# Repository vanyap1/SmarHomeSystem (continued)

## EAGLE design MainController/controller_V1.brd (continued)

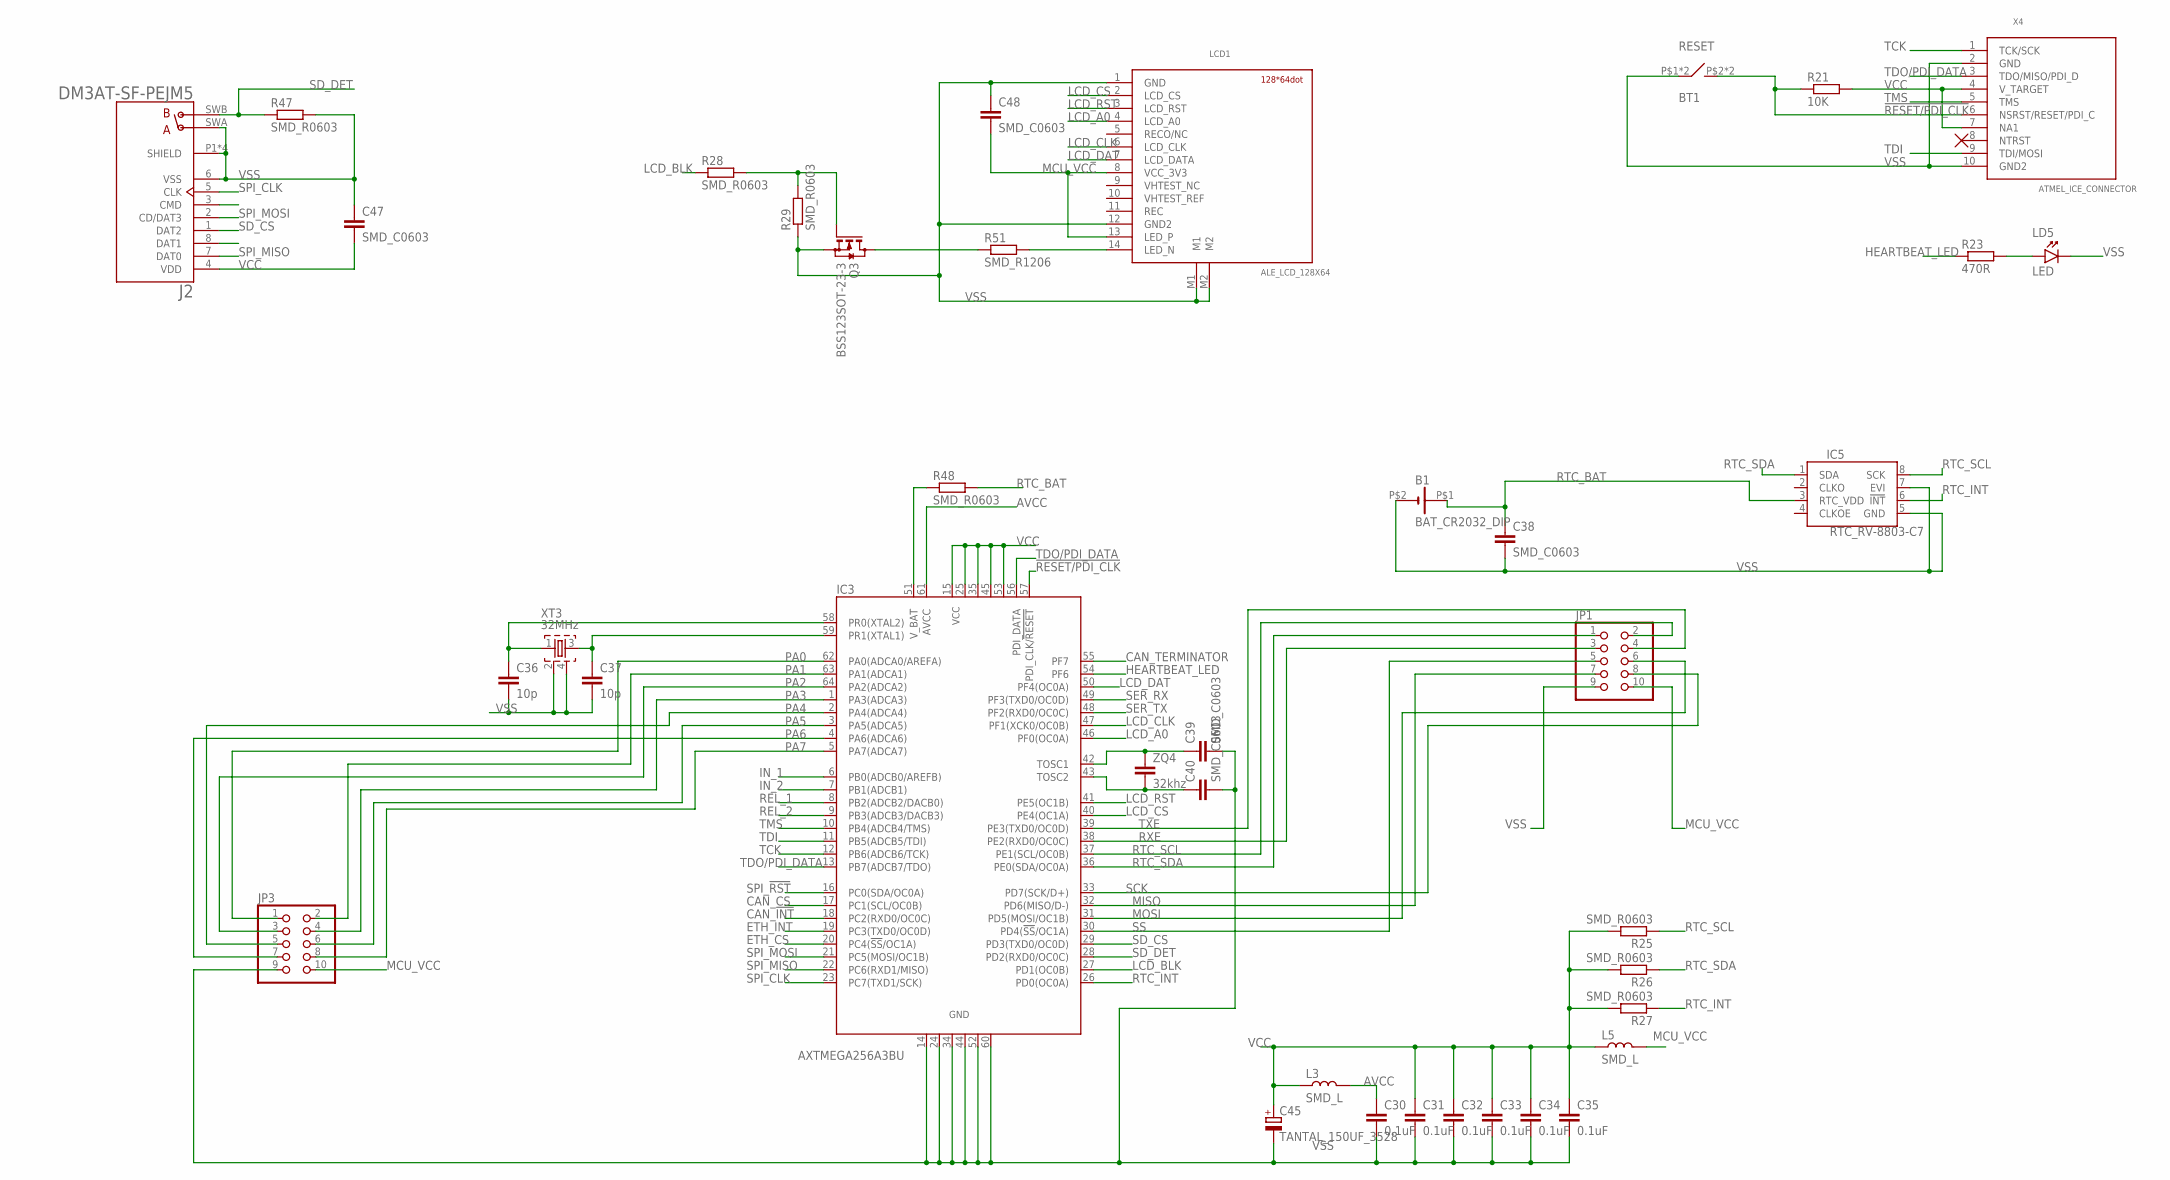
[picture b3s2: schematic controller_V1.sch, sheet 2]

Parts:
B1: BAT_CR2032_DIP; CR2032_DIP
BT1: RESET; 5X5MM_SMD_CY
C30, C31, C32, C33, C34, C35: 0.1uF; 0603
C36, C37: 10p; 0603
C38, C39, C40, C47, C48: SMD_C0603; 0603
C45: TANTAL_150UF_3528; KA-3528ASYC
IC3: AXTMEGA256A3BU; TQFP64
IC5: RTC_RV-8803-C7; C7_RTC
J2: DM3AT-SF-PEJM5; HRS_DM3AT-SF-PEJM5
JP1, JP3: PINHD-2X5; 2X05
L3, L5: SMD_L; 0805
LCD1: ALE_LCD_128X64; ALE_LCD_14PIN_CONNECTOR
LD5: LED; 3MM_DIP_LED
Q3: BSS123SOT-23-3; SOT-23(3)
R21: 10K; 0603
R23: 470R; 0603
R25, R26, R27, R28, R29, R47, R48: SMD_R0603; 0603
R51: SMD_R1206; 1206
X4: ATMEL_ICE_CONNECTOR; MINI10P_SPI/JTAG/PDI
XT3: 32MHz; QUARTZ_3X3MM
ZQ4: 32khz; 1206

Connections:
!RESET/PDI_CLK: BT1.P$2 (4), BT1.P$3 (4), IC3.57 (PDI_CLK/!RESET!), R21.1, X4.6 (NSRST/RESET/PDI_C)
AVCC: C30.1, IC3.61 (AVCC), L3.2
CAN_!INT: IC3.18 (PC2(RXD0/OC0C)); also elsewhere on the board
CAN_CS: IC3.17 (PC1(SCL/OC0B)); also elsewhere on the board
CAN_TERMINATOR: IC3.55 (PF7); also elsewhere on the board
ETH_CS: IC3.20 (PC4(!SS!/OC1A)); also elsewhere on the board
ETH_INT: IC3.19 (PC3(TXD0/OC0D)); also elsewhere on the board
HEARTBEAT_LED: IC3.54 (PF6), R23.1
IN_1: IC3.6 (PB0(ADCB0/AREFB)); also elsewhere on the board
IN_2: IC3.7 (PB1(ADCB1)); also elsewhere on the board
LCD_A0: IC3.46 (PF0(OC0A)), LCD1.4 (LCD_A0)
LCD_BLK: IC3.27 (PD1(OC0B)), R28.1
LCD_CLK: IC3.47 (PF1(XCK0/OC0B)), LCD1.6 (LCD_CLK)
LCD_CS: IC3.40 (PE4(OC1A)), LCD1.2 (LCD_CS)
LCD_DAT: IC3.50 (PF4(OC0A)), LCD1.7 (LCD_DATA)
LCD_RST: IC3.41 (PE5(OC1B)), LCD1.3 (LCD_RST)
MCU_VCC: C48.2, JP1.10, JP3.10, L5.2, LCD1.8 (VCC_3V3), LCD1.13 (LED_P); also elsewhere on the board
MISO: IC3.32 (PD6(MISO/D-)), JP1.7
MOSI: IC3.31 (PD5(MOSI/OC1B)), JP1.6
unnamed: C36.1, IC3.58 (PR0(XTAL2)), XT3.1
unnamed: C37.1, IC3.59 (PR1(XTAL1)), XT3.3
unnamed: LD5.A, R23.2
unnamed: IC3.51 (V_BAT), R48.1
unnamed: Q3.3 (D), R51.1
unnamed: LCD1.14 (LED_N), R51.2
unnamed: C40.1, IC3.43 (TOSC2), ZQ4.2
unnamed: C39.1, IC3.42 (TOSC1), ZQ4.1
unnamed: Q3.1 (G), R28.2, R29.2
PA0: IC3.62 (PA0(ADCA0/AREFA)), JP3.1
PA1: IC3.63 (PA1(ADCA1)), JP3.2
PA2: IC3.64 (PA2(ADCA2)), JP3.3
PA3: IC3.1 (PA3(ADCA3)), JP3.4
PA4: IC3.2 (PA4(ADCA4)), JP3.5
PA5: IC3.3 (PA5(ADCA5)), JP3.6
PA6: IC3.4 (PA6(ADCA6)), JP3.7
PA7: IC3.5 (PA7(ADCA7)), JP3.8
REL_1: IC3.8 (PB2(ADCB2/DACB0)); also elsewhere on the board
REL_2: IC3.9 (PB3(ADCB3/DACB3)); also elsewhere on the board
RTC_BAT: B1.P$1 (+), C38.1, IC5.3 (RTC_VDD), R48.2
RTC_INT: IC3.26 (PD0(OC0A)), IC5.6 (!INT), R27.1
RTC_SCL: IC3.37 (PE1(SCL/OC0B)), IC5.8 (SCK), JP1.2, R25.1; also elsewhere on the board
RTC_SDA: IC3.36 (PE0(SDA/OC0A)), IC5.1 (SDA), JP1.1, R26.1; also elsewhere on the board
RXE: IC3.38 (PE2(RXD0/OC0C)), JP1.3
SCK: IC3.33 (PD7(SCK/D+)), JP1.8
SD_CS: IC3.29 (PD3(TXD0/OC0D)), J2.1 (DAT2)
SD_DET: IC3.28 (PD2(RXD0/OC0C)), J2.SWB (B), R47.1
SER_RX: IC3.49 (PF3(TXD0/OC0D)); also elsewhere on the board
SER_TX: IC3.48 (PF2(RXD0/OC0C)); also elsewhere on the board
SPI_!RST: IC3.16 (PC0(SDA/OC0A)); also elsewhere on the board
SPI_CLK: IC3.23 (PC7(TXD1/SCK)), J2.5 (CLK); also elsewhere on the board
SPI_MISO: IC3.22 (PC6(RXD1/MISO)), J2.7 (DAT0); also elsewhere on the board
SPI_MOSI: IC3.21 (PC5(MOSI/OC1B)), J2.2 (CD/DAT3); also elsewhere on the board
SS: IC3.30 (PD4(!SS!/OC1A)), JP1.5
TCK: IC3.12 (PB6(ADCB6/TCK)), X4.1 (TCK/SCK)
TDI: IC3.11 (PB5(ADCB5/TDI)), X4.9 (TDI/MOSI)
TDO/PDI_DATA: IC3.13 (PB7(ADCB7/TDO)), IC3.56 (PDI_DATA), X4.3 (TDO/MISO/PDI_D)
TMS: IC3.10 (PB4(ADCB4/TMS)), X4.5 (TMS)
TXE: IC3.39 (PE3(TXD0/OC0D)), JP1.4
VCC: C31.1, C32.1, C33.1, C34.1, C35.1, C45.P (+), C47.2, IC3.15 (VCC1), IC3.25 (VCC2), IC3.35 (VCC3), IC3.45 (VCC4), IC3.53 (VCC5), J2.4 (VDD), L3.1, L5.1, R21.2, R25.2, R26.2, R27.2, X4.4 (V_TARGET), X4.7 (NA1); also elsewhere on the board
VSS: B1.P$2 (-), BT1.P$1 (1), BT1.P$4 (1), C30.2, C31.2, C32.2, C33.2, C34.2, C35.2, C36.2, C37.2, C38.2, C39.2, C40.2, C45.M (-), C47.1, C48.1, IC3.14 (GND1), IC3.24 (GND2), IC3.34 (GND3), IC3.44 (GND4), IC3.52 (GND5), IC3.60 (GND6), IC5.5 (GND), IC5.7 (EVI), J2.6 (VSS), J2.P1 (SHIELD), J2.P2 (SHIELD), J2.P3 (SHIELD), J2.P4 (SHIELD), J2.SWA (A), JP1.9, JP3.9, LCD1.1 (GND), LCD1.12 (GND2), LCD1.M1, LCD1.M2, LD5.K, Q3.2 (S), R29.1, R47.2, X4.2 (GND), X4.10 (GND2), XT3.2, XT3.4; also elsewhere on the board

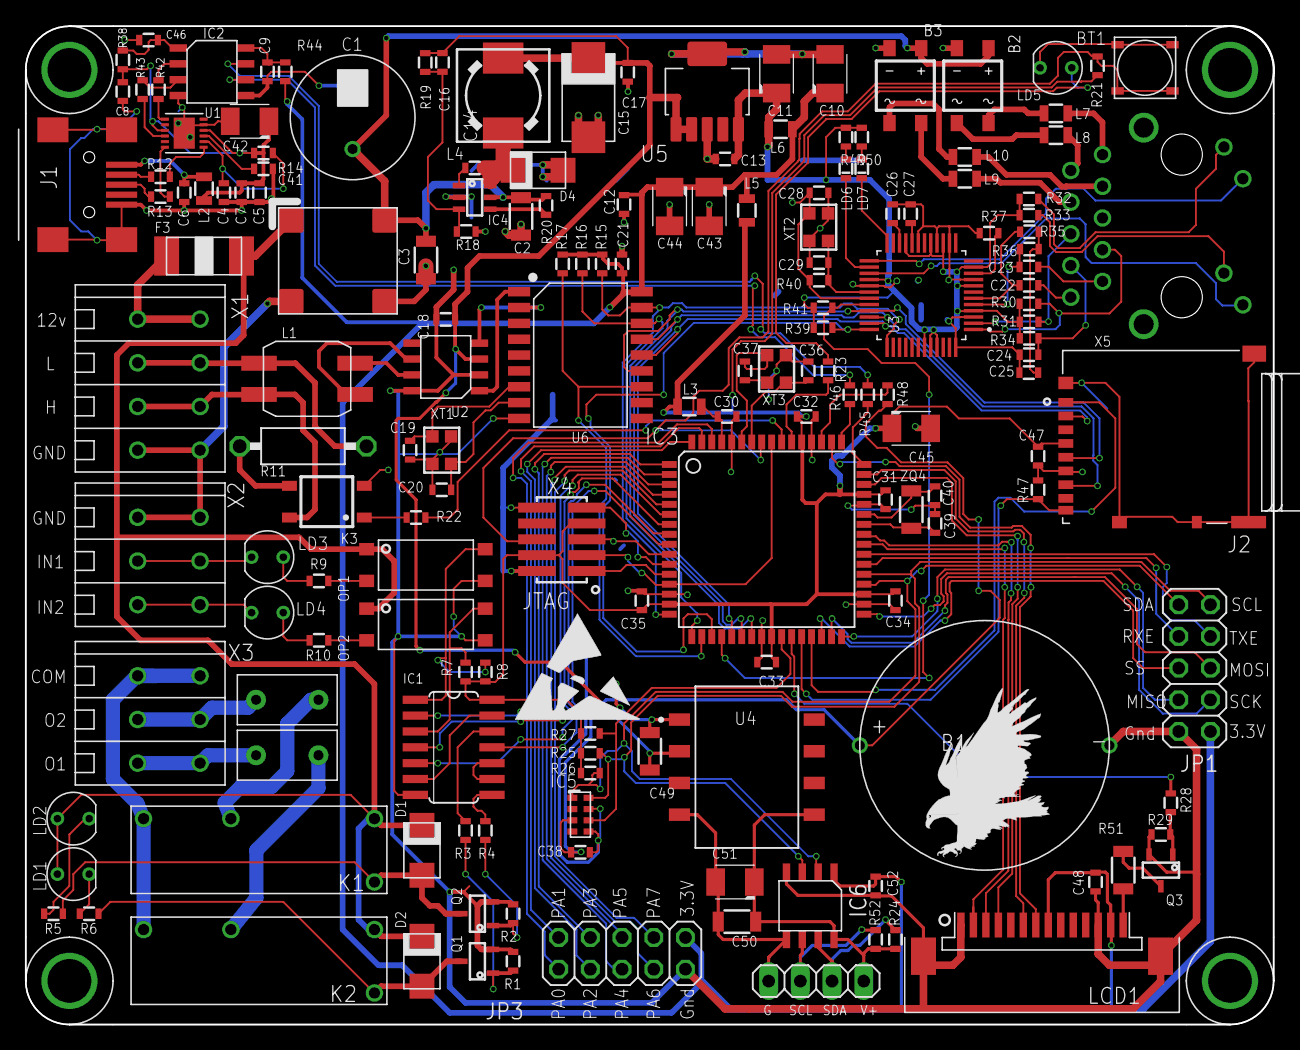
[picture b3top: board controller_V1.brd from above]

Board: 2 copper layers, 100.0 x 80.0 mm, 171 parts (1 on the bottom side), 153 nets.

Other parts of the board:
U$2, U$4: EAGLE-PLC-10MM
U$3: ESD_10.00

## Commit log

2023-08-16 project upload
2023-08-19 add new files
2023-10-16 can bridge controller update
2023-10-16 added missing font files
2023-10-16 change pump indicator current limit
2024-02-06 added pump controll CAN_ID 0x043[1] pump current from BPSU
2024-02-06 removed not actual project data
2024-04-09 added sensor unit
2024-04-09 Added CAN bus Sensor unit
2024-04-10 added main controller schematic diagram
2024-04-13 update PSU and Bridge module
2024-10-05 project update
